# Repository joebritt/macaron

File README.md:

Macaron is an Arduino shield based on the Petit Biscuit educational Arduino board.

Inspired by Saandial’s Petit Biscuit 
(https://www.tindie.com/products/saandial/petit-biscuit-arduino-programming/). 

Petit Biscuit was designed by Saandial as a tool for introductory embedded programming
using the Arduino IDE. There are 2 versions.

The "saveur fraise" model has:
  16 LEDs (4 red, 4 yellow, 4 green, 4 blue)
  2 momentary pushbuttons
  Atmel ATMega328P with Arduino bootloader
  Reset button
  Crystal
  Header for FTDI-style serial interface

The "saveur vanille" model has mostly the same parts, but these differences:
  Only 15 LEDs (3 red, 4 yellow, 4 green, 4 blue)
  Potentiometer
  Slide switch

I think these were great little boards for teaching basic embedded programming. It's very
easy to see how the I/O pins connect to the LEDs, switches, and potentiometer, and easy to
understand how the software interacts with and controls them. 
Saandial, thank you for designing these!!

I decided to build my own version for my kids (and myself :-), partly because I had some small
linear potentiometers I wanted to use and partly because I wanted to try some interesting
looking surface mount high-efficiency LEDs.

The result is Macaron, a bit of a hybrid of the Vanille and Fraise Petit Biscuits, and built
as an Arduino Shield.

Some notes:

The LEDs are all on dedicated I/O pins, so they can always be directly controlled.
The LED on the linear potentiometer slider is connected to the Arduino TX line. It will flicker
when there is serial traffic. You can also just turn the TX line (1) into an digital output
and control it directly.

The potentiometer is connected to A5. There is also a button between A5 and ground. Normally you
will use analogRead( A5 ) to get the slider position (0-1023). If you push the A5 button, it will
pull A5 to ground, and you'll read 0. You can use the very cool Arduino map() function to map the
0-1023 value onto any other range you want -- or even reverse the range.

The other button is simply connected to digital pin 2, so you can just configure it as an input
with pullup and use digitalRead(2) to get it's state. If it's down, it will read as 0 (or false).

Though designed as an Uno shield, Macaron can also be used with an Arduino Mega, which will provide 
additional I/O pins so more things can be added. 

The board uses very bright high-efficiency LEDs from Avago/Broadcom and a linear potentiometer from Bourns. 

All parts are available from Mouser.  Mouser part numbers below: 

630-ALMD-EG2E-XZ002 Red LED 
630-ALMD-EL2E-XZ002 Amber LED 
630-ALMD-CM2F-12002 Green LED 
630-ALMD-CB2E-UV002 Blue LED 
652-PTL30-10G1-103B2 10K linear (slide) potentiometer with LED 

Headers are normal 0.1" single row.
2 tactile buttons are generic.

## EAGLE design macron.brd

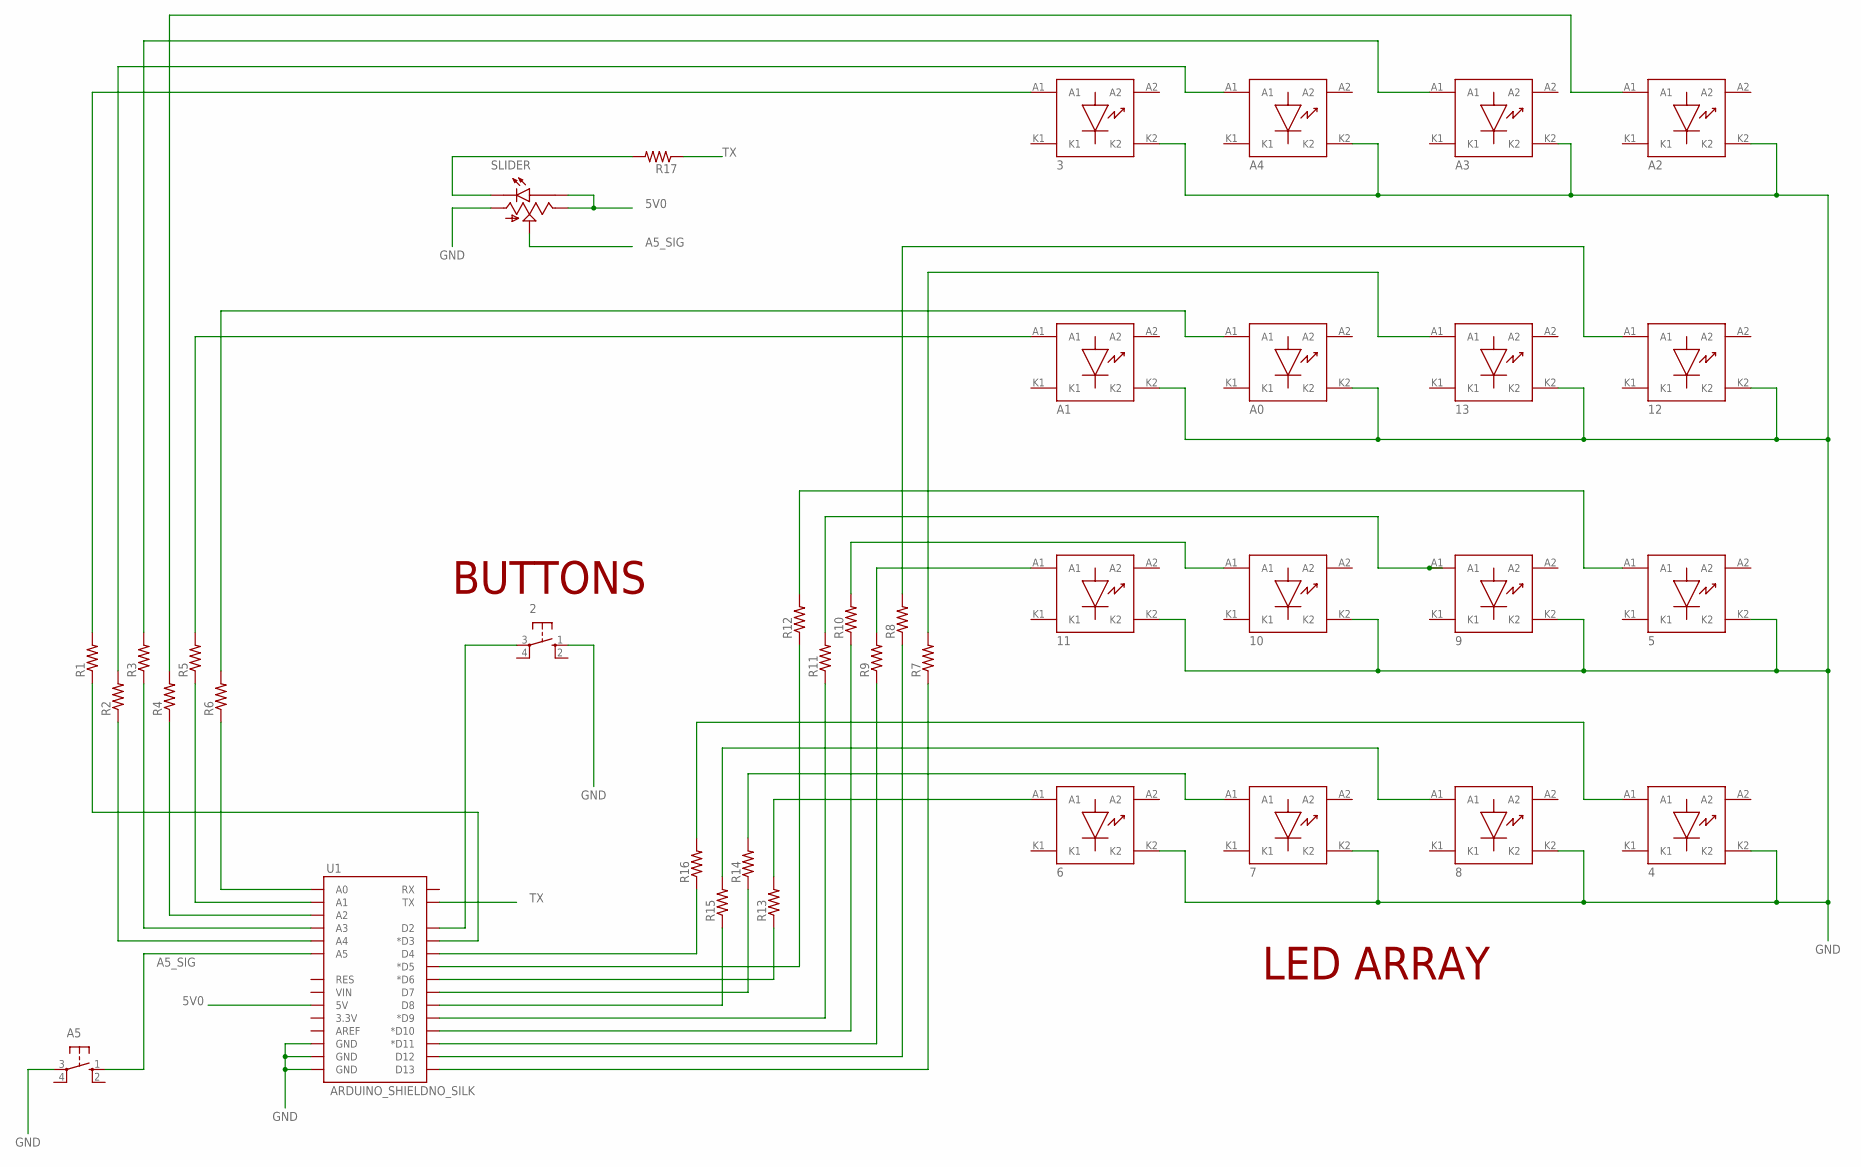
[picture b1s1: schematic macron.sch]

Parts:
2: 10-XX; B3F-10XX
3, 4, 5, 6, 7, 8, 9, 10, 11, 12, 13: LED_SMT; AVAGO-SMT-LED
A0, A1, A2, A3, A4: LED_SMT; AVAGO-SMT-LED
A5: 10-XX; B3F-10XX
R1, R2, R3, R4, R5, R6, R7, R8, R9, R10, R11, R12, R13, R14, R15, R16, R17: R-US_0204/7; 0204/7
SLIDER: BOURNS_LED_SLIDER; BOURNS_45MM_LED_SLIDE_POT
U1: ARDUINO_SHIELDNO_SILK; DUEMILANOVE_VIAS

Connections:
5V0: SLIDER.HIGH_END (HIGH), SLIDER.LED+ (A1), U1.5V
A5_SIG: A5.1 (S), SLIDER.WIPER, U1.A5
GND: 2.1 (S), 3.K2, 4.K2, 5.K2, 6.K2, 7.K2, 8.K2, 9.K2, 10.K2, 11.K2, 12.K2, 13.K2, A0.K2, A1.K2, A2.K2, A3.K2, A4.K2, A5.3, SLIDER.LOW_END (LOW), U1.GND@0 (GND), U1.GND@1 (GND), U1.GND@2 (GND)
unnamed: R17.2, SLIDER.LED- (C)
unnamed: 3.A1, R1.2
unnamed: R2.1, U1.A4
unnamed: A4.A1, R2.2
unnamed: R3.1, U1.A3
unnamed: A3.A1, R3.2
unnamed: R4.1, U1.A2
unnamed: A2.A1, R4.2
unnamed: R5.1, U1.A1
unnamed: R6.1, U1.A0
unnamed: A1.A1, R5.2
unnamed: A0.A1, R6.2
unnamed: R7.1, U1.D13
unnamed: R8.1, U1.D12
unnamed: R9.1, U1.D11 (*D11)
unnamed: R10.1, U1.D10 (*D10)
unnamed: R11.1, U1.D9 (*D9)
unnamed: 13.A1, R7.2
unnamed: 12.A1, R8.2
unnamed: 11.A1, R9.2
unnamed: 10.A1, R10.2
unnamed: 9.A1, R11.2
unnamed: R12.1, U1.D5 (*D5)
unnamed: R13.1, U1.D6 (*D6)
unnamed: R14.1, U1.D7
unnamed: R15.1, U1.D8
unnamed: R16.1, U1.D4
unnamed: 5.A1, R12.2
unnamed: 6.A1, R13.2
unnamed: 7.A1, R14.2
unnamed: 8.A1, R15.2
unnamed: 4.A1, R16.2
unnamed: 2.3, U1.D2
unnamed: R1.1, U1.D3 (*D3)
TX: R17.1, U1.TX

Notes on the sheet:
BUTTONS
LED ARRAY

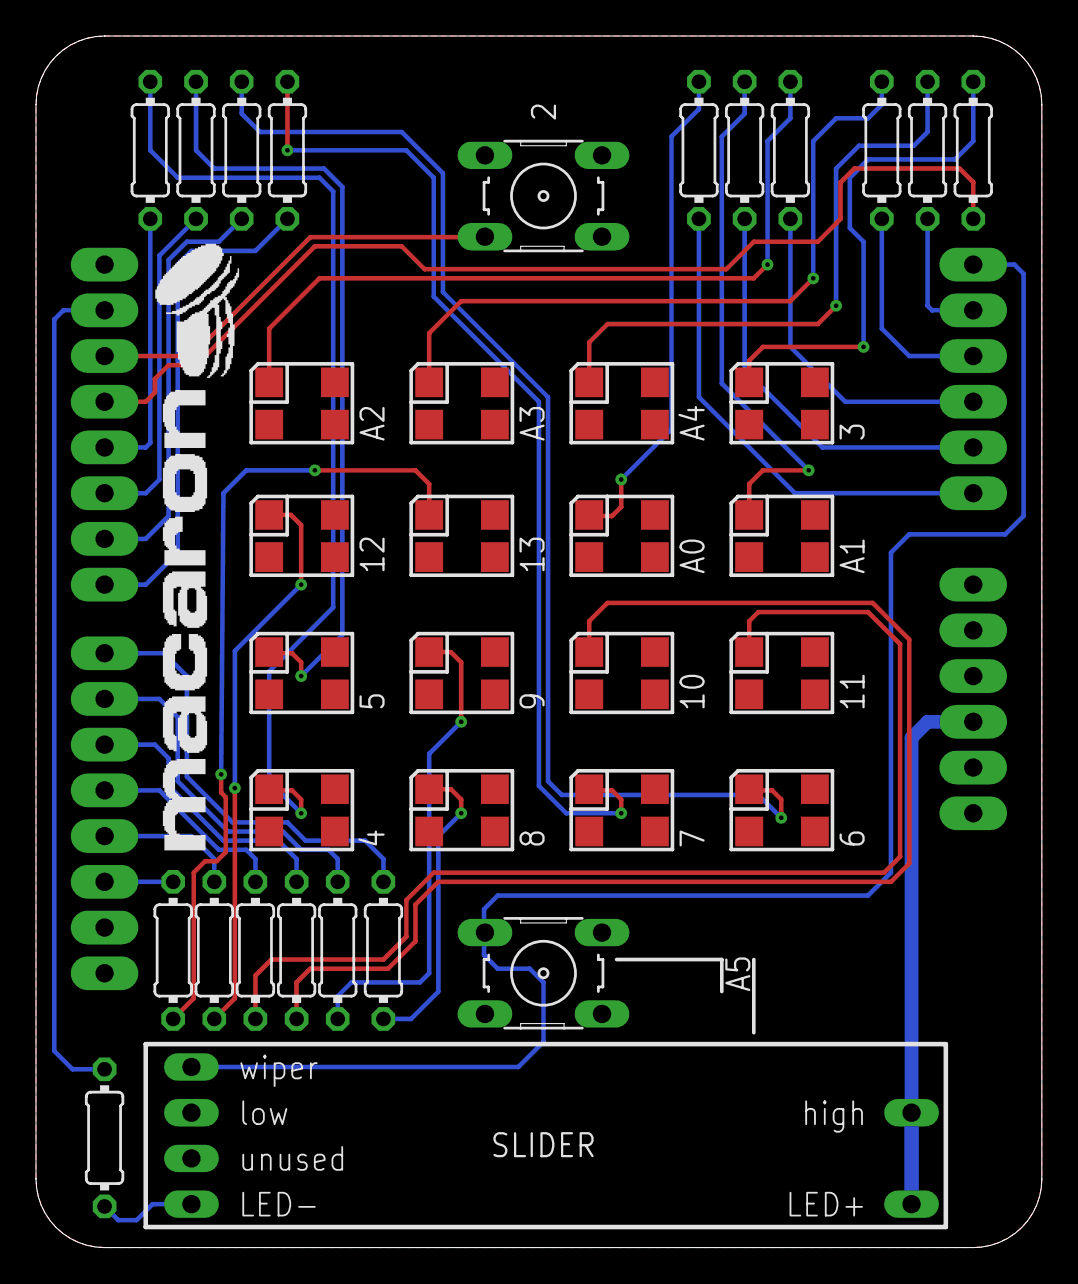
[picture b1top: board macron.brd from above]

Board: 2 copper layers, 55.9 x 67.3 mm, 37 parts (0 on the bottom side), 38 nets.

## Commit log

2018-01-02 Eagle files for macron
2018-08-31 Add files via upload
    Eagle schematic and board files.
2018-08-31 Delete macron.brd
    uploaded newer files in Macron hardware directory
2018-08-31 Delete macron.sch
    uploaded latest eagle files in Macron Hardware directory
2018-08-31 Add files via upload
    Arduino demo sketches for Macaron
2018-09-01 Add files via upload
    Added PDFs of schematic & board top/bottom.
2018-09-01 Add files via upload
    Bigger board PDFs.

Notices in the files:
parts and their libraries:
modified_sparkfun_joe: Licensing: Creative Commons ShareAlike 4.0 International - https://creativecommons.org/licenses/by-sa/4.0
